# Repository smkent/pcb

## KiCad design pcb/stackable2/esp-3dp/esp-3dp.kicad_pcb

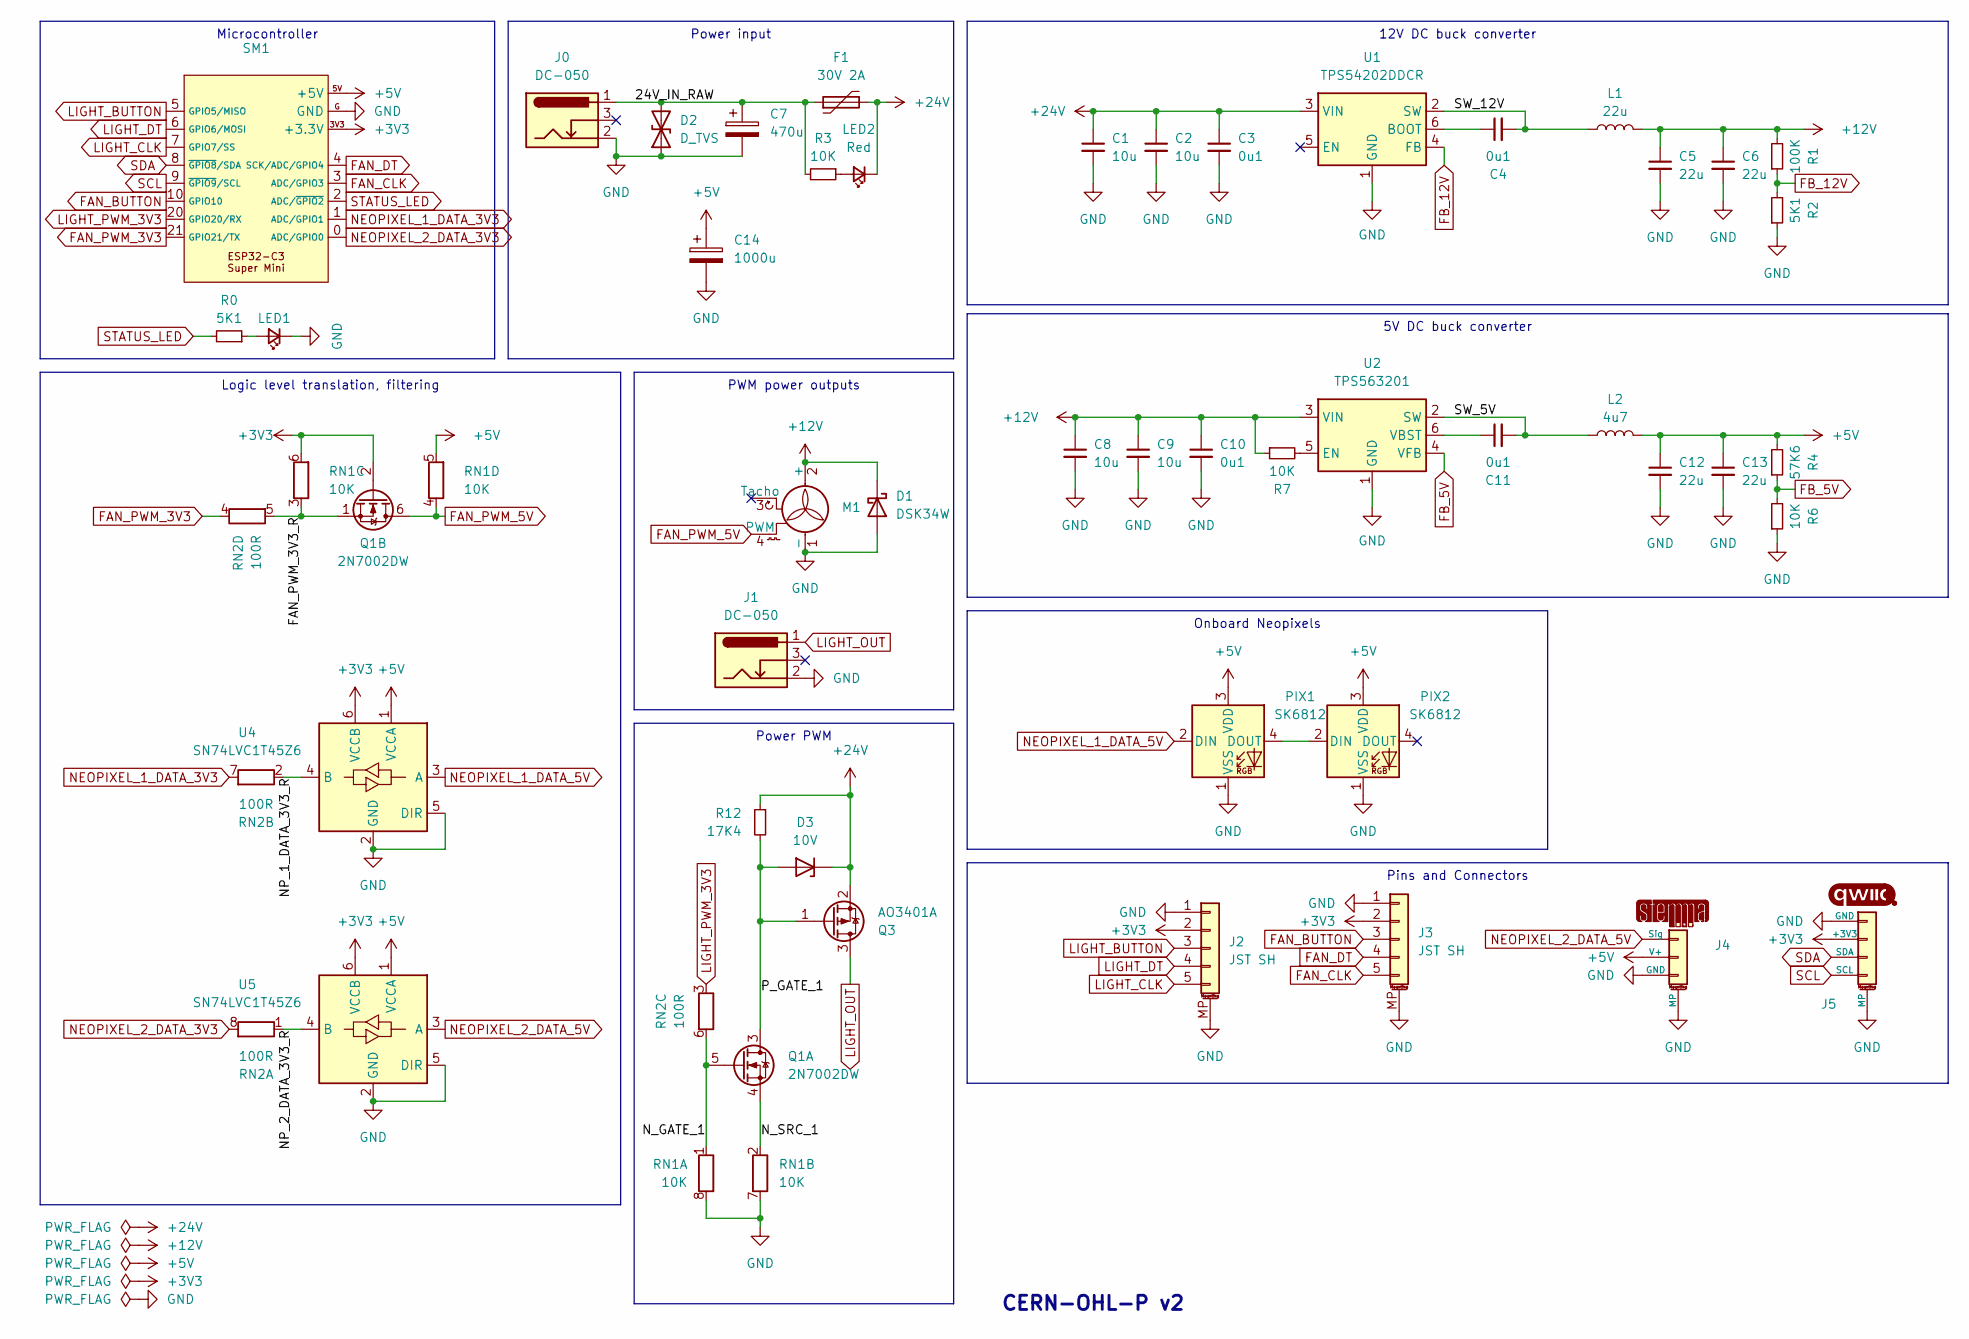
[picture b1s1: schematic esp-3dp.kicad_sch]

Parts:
C1, C2, C8, C9: 10u; C_0603_1608Metric
C3, C4, C10, C11: 0u1; C_0402_1005Metric
C5, C6: 22u; C_0805_2012Metric
C7: 470u; CP_Elec_8x10
C12, C13: 22u; C_0603_1608Metric
C14: 1000u; CP_Elec_8x10
D1: DSK34W; D_SOD-123F
D2: D_TVS; D_SOD-123F
D3: 10V; D_SOD-523
F1: 30V 2A; Fuse_1812_4532Metric
J0, J1: DC-050; BarrelJack_DC-050_SMT_Horizontal
J2, J3: JST SH; JST_SH_SM05B-SRSS-TB_1x05-1MP_P1.00mm_Horizontal
J4: STEMMA-Signal; STEMMA-Signal-SMD-horizontal
J5: Qwiic; Qwiic-SMD-horizontal
L1: 22u; L_Power_7.0x6.6mm_0630
L2: 4u7; L_1008_2520Metric
LED1: LED_Small; LED_0603_1608Metric
LED2: Red; LED_0402_1005Metric
M1: KF2510; FanPinHeader_1x04_P2.54mm_Horizontal
PIX1, PIX2: SK6812; LED_SK6812_PLCC4_5.0x5.0mm_P3.2mm
Q1: 2N7002DW; SOT-363_SC-70-6_HandSolder; LCSC Part C5190214
Q3: AO3401A; SOT-23
R0: 5K1; R_0603_1608Metric
R1: 100K; R_0402_1005Metric
R2: 5K1; R_0402_1005Metric
R3, R6, R7: 10K; R_0402_1005Metric
R4: 57K6; R_0402_1005Metric
R12: 17K4; R_0603_1608Metric
RN1: 10K; R_Array_Convex_4x0603_HandSolder
RN2: 100R; R_Array_Convex_4x0603_HandSolder
SM1: ESP32-C3-Super-Mini-Castellated-SMD-only
U1: TPS54202DDCR; SOT-23-6; LCSC Part C191884
U2: TPS563201; SOT-23-6
U4, U5: SN74LVC1T45Z6; SOT-563; LCSC Part C441819

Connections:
+3V3: J2.2, J3.2, J5.2 (+3V3), Q1.2 (G), RN1.6 (R3.2), SM1.3V3 (+3.3V), U4.6 (VCCB), U5.6 (VCCB)
+5V: C12.1, C13.1, C14.1, J4.2 (V+), L2.2, PIX1.3 (VDD), PIX2.3 (VDD), R4.2, RN1.5 (R4.2), SM1.5V (+5V), U4.1 (VCCA), U5.1 (VCCA)
+12V: C5.1, C6.1, C8.1, C9.1, C10.1, D1.1 (K), L1.2, M1.2 (+), R1.2, R7.1, U2.3 (VIN)
+24V: C1.1, C2.1, C3.1, D3.1 (K), F1.2, LED2.1 (K), Q3.2 (S), R12.1, U1.3 (VIN)
/24V_IN_RAW: C7.1, D2.2 (A2), F1.1, J0.1, R3.2
/FAN_PWM_3V3_R: Q1.1 (S), RN1.3 (R3.1), RN2.5 (R4.2)
/NP_1_DATA_3V3_R: RN2.2 (R2.1), U4.4 (B)
/NP_2_DATA_3V3_R: RN2.1 (R1.1), U5.4 (B)
/N_GATE_1: Q1.5 (G), RN1.1 (R1.1), RN2.6 (R3.2)
/N_SRC_1: Q1.4 (S), RN1.2 (R2.1)
/P_GATE_1: D3.2 (A), Q1.3 (D), Q3.1 (G), R12.2
/SW_5V: C11.2, L2.1, U2.2 (SW)
/SW_12V: C4.2, L1.1, U1.2 (SW)
FAN_BUTTON: J3.3, SM1.10 (GPIO10)
FAN_CLK: J3.5, SM1.3 (ADC/GPIO3)
FAN_DT: J3.4, SM1.4 (SCK/ADC/GPIO4)
FAN_PWM_3V3: RN2.4 (R4.1), SM1.21 (GPIO21/TX)
FAN_PWM_5V: M1.4 (PWM), Q1.6 (D), RN1.4 (R4.1)
FB_5V: R4.1, R6.2, U2.4 (VFB)
FB_12V: R1.1, R2.2, U1.4 (FB)
GND: C1.2, C2.2, C3.2, C5.2, C6.2, C7.2, C8.2, C9.2, C10.2, C12.2, C13.2, C14.2, D1.2 (A), D2.1 (A1), J0.2, J1.2, J2.1, J2.MP (MountPin), J3.1, J3.MP (MountPin), J4.3 (GND), J4.MP, J5.1 (GND), J5.MP, LED1.1 (K), M1.1 (-), PIX1.1 (VSS), PIX2.1 (VSS), R2.1, R6.1, RN1.7 (R2.2), RN1.8 (R1.2), SM1.G (GND), U1.1 (GND), U2.1 (GND), U4.2 (GND), U4.5 (DIR), U5.2 (GND), U5.5 (DIR)
LIGHT_BUTTON: J2.3, SM1.5 (GPIO5/MISO)
LIGHT_CLK: J2.5, SM1.7 (GPIO7/SS)
LIGHT_DT: J2.4, SM1.6 (GPIO6/MOSI)
LIGHT_OUT: J1.1, Q3.3 (D)
LIGHT_PWM_3V3: RN2.3 (R3.1), SM1.20 (GPIO20/RX)
NEOPIXEL_1_DATA_3V3: RN2.7 (R2.2), SM1.1 (ADC/GPIO1)
NEOPIXEL_1_DATA_5V: PIX1.2 (DIN), U4.3 (A)
NEOPIXEL_2_DATA_3V3: RN2.8 (R1.2), SM1.0 (ADC/GPIO0)
NEOPIXEL_2_DATA_5V: J4.1 (Sig), U5.3 (A)
unnamed: LED1.2 (A), R0.1
unnamed: LED2.2 (A), R3.1
unnamed: PIX1.4 (DOUT), PIX2.2 (DIN)
unnamed: C4.1, U1.6 (BOOT)
unnamed: R7.2, U2.5 (EN)
unnamed: C11.1, U2.6 (VBST)
SCL: J5.4 (SCL), SM1.9 (~GPIO9/SCL)
SDA: J5.3 (SDA), SM1.8 (~GPIO8/SDA)
STATUS_LED: R0.2, SM1.2 (ADC/~GPIO2)

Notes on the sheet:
5V DC buck converter
Power input
12V DC buck converter
Microcontroller
PWM power outputs
Onboard Neopixels
Pins and Connectors
Logic level translation, filtering
Power PWM
CERN-OHL-P v2

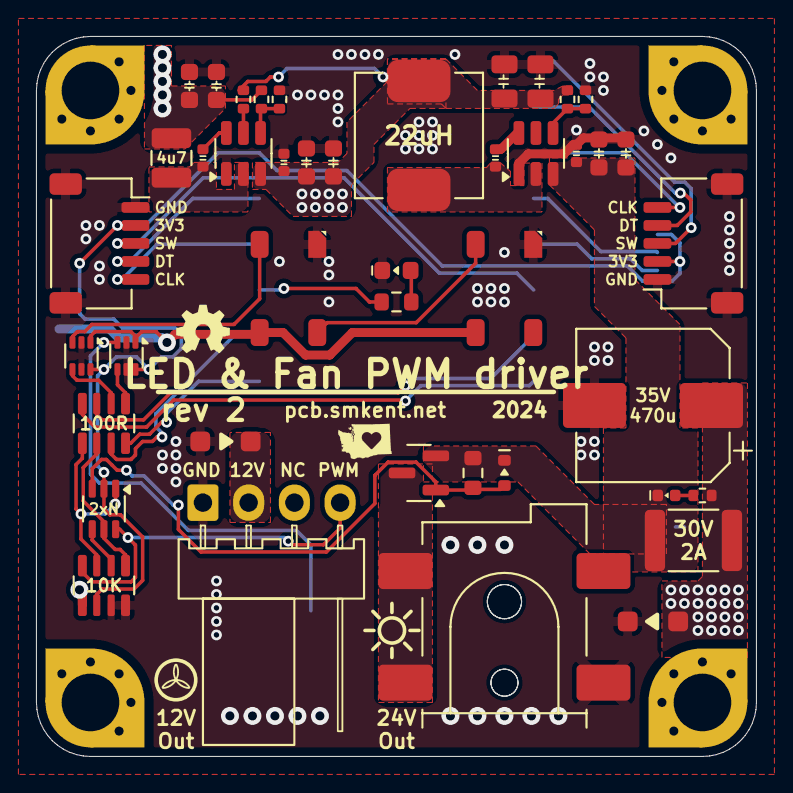
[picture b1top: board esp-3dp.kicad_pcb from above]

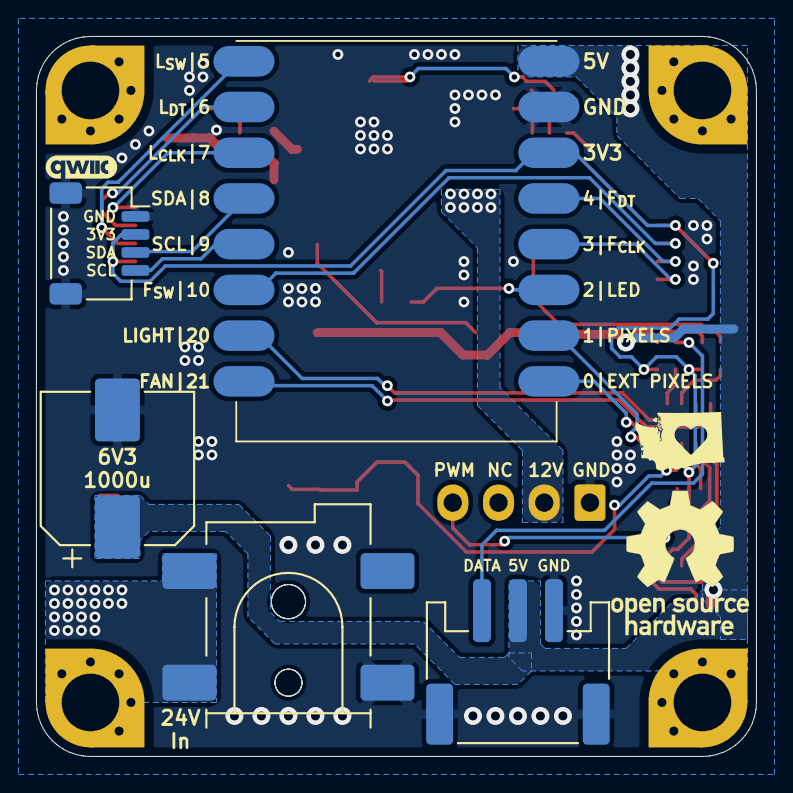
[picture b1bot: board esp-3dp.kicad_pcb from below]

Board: 2 copper layers, 40.0 x 40.0 mm, 52 parts (5 on the bottom side), 39 nets.

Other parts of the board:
MH_NE: MountingHole_3.2mm_M3_Pad_Via_corner_compact
MH_NW: MountingHole_3.2mm_M3_Pad_Via_corner_compact
MH_SE: MountingHole_3.2mm_M3_Pad_Via_corner_compact
MH_SW: MountingHole_3.2mm_M3_Pad_Via_corner_compact

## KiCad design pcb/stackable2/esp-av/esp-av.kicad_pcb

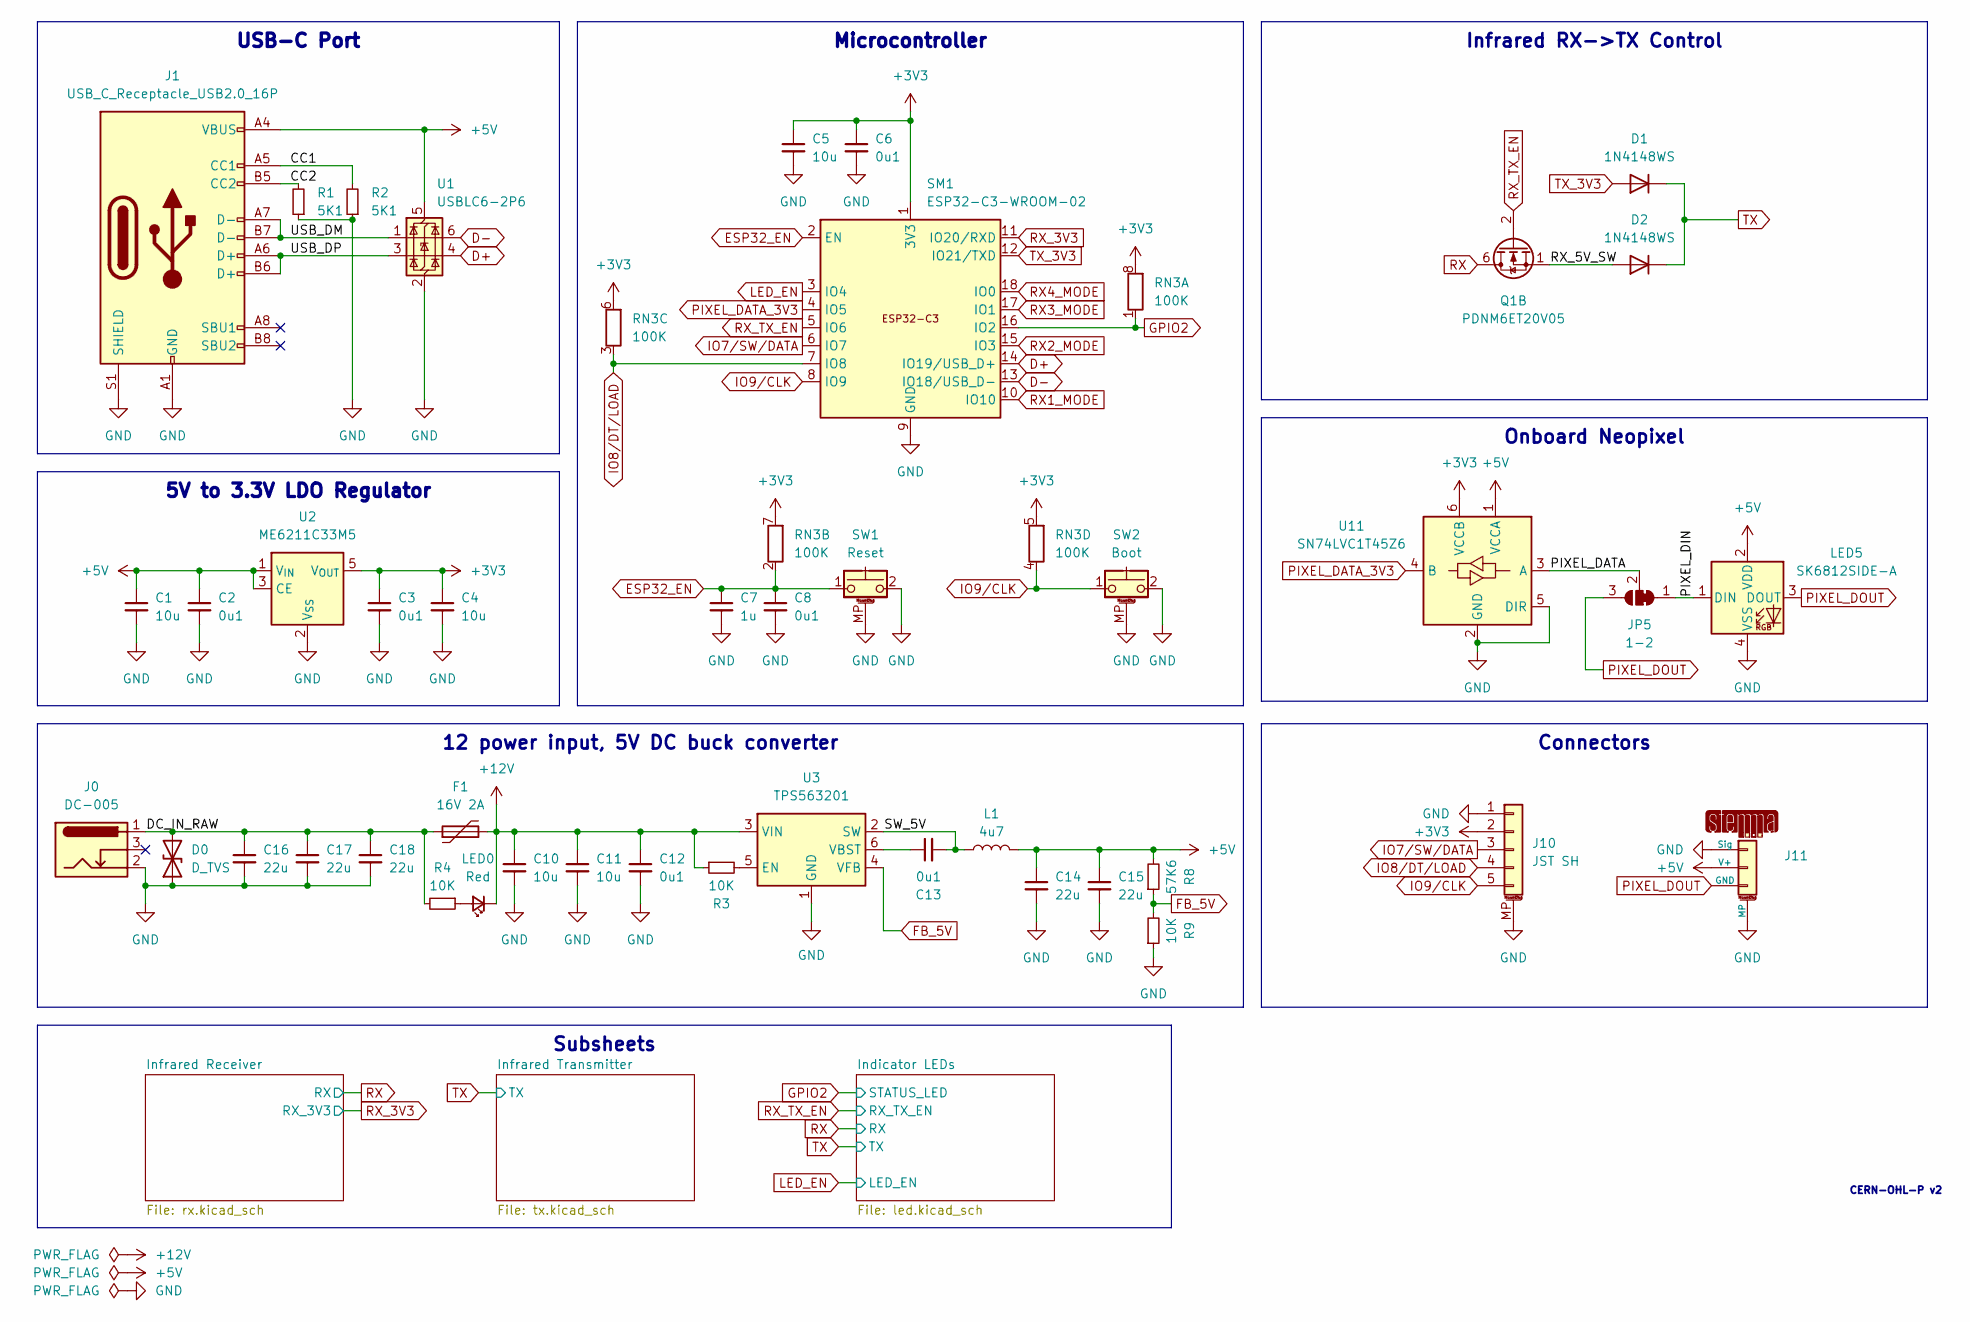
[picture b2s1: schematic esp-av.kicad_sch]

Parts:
C1, C4, C5, C10, C11: 10u; C_0603_1608Metric
C2, C3, C6, C8, C12, C13: 0u1; C_0603_1608Metric
C7: 1u; C_0603_1608Metric
C14, C15, C16, C17, C18: 22u; C_0603_1608Metric
D0: D_TVS; D_SOD-123F; LCSC Part C7473216
D1, D2: 1N4148WS; D_SOD-323
F1: 16V 2A; Fuse_1206_3216Metric; LCSC Part C2982271
J0: DC-005; BarrelJack_DC-005_THT_Horizontal
J1: USB_C_Receptacle_USB2.0_16P; USB_C_Receptacle_GCT_USB4105-xx-A_16P_TopMnt_Horizontal; LCSC Part C2765186
J10: JST SH; JST_SH_SM05B-SRSS-TB_1x05-1MP_P1.00mm_Horizontal
J11: STEMMA-Signal; STEMMA-Signal-SMD-horizontal
JP5: 1-2; SolderJumper-3_P1.3mm_Bridged12_RoundedPad1.0x1.5mm
L1: 4u7; L_1008_2520Metric; LCSC Part C22471106
LED0: Red; LED_0603_1608Metric
LED5: SK6812SIDE-A; LED_SK6812SIDE-A_4.0x1.6mm; LCSC Part C2890037
Q1: PDNM6ET20V05; SOT-563; LCSC Part C918811
R1, R2: 5K1; R_0603_1608Metric
R3, R4, R9: 10K; R_0603_1608Metric
R8: 57K6; R_0603_1608Metric
RN3: 100K; R_Array_Convex_4x0603_HandSolder
SM1: ESP32-C3-WROOM-02
SW1: Reset; SW_Push_1P1T-MP_NO_4.6x3mm_Horizontal
SW2: Boot; SW_Push_1P1T_NO_3.3x3.3mm_MP
U1: USBLC6-2P6; SOT-666; LCSC Part C29780639
U2: ME6211C33M5; SOT-23-5; LCSC Part C82942
U3: TPS563201; SOT-23-6; LCSC Part C116592
U11: SN74LVC1T45Z6; SOT-563; LCSC Part C441819

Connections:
+3V3: C3.1, C4.1, C5.1, C6.1, J10.2, RN3.5 (R4.2), RN3.6 (R3.2), RN3.7 (R2.2), RN3.8 (R1.2), SM1.1 (3V3), U2.5 (V_{OUT}), U11.6 (VCCB); also elsewhere on the board
+5V: C1.1, C2.1, C14.1, C15.1, J1.A4 (VBUS), J1.A9 (VBUS), J1.B4 (VBUS), J1.B9 (VBUS), J11.2 (V+), L1.2, LED5.2 (VDD), R8.2, U1.5 (VBUS), U2.1 (V_{IN}), U2.3 (CE), U11.1 (VCCA); also elsewhere on the board
+12V: C10.1, C11.1, C12.1, F1.2, LED0.1 (K), R3.1, U3.3 (VIN)
/CC1: J1.A5 (CC1), R2.2
/CC2: J1.B5 (CC2), R1.2
/DC_IN_RAW: C16.1, C17.1, C18.1, D0.2 (A2), F1.1, J0.1, R4.2
/PIXEL_DATA: JP5.2 (C), U11.3 (A)
/PIXEL_DIN: JP5.1 (A), LED5.1 (DIN)
/RX_5V_SW: D2.2 (A), Q1.1 (S)
/SW_5V: C13.2, L1.1, U3.2 (SW)
/USB_DM: J1.A7 (D-), J1.B7 (D-), U1.1 (I/O1)
/USB_DP: J1.A6 (D+), J1.B6 (D+), U1.3 (I/O2)
D+: SM1.14 (IO19/USB_D+), U1.4 (I/O2)
D-: SM1.13 (IO18/USB_D-), U1.6 (I/O1)
ESP32_EN: C7.1, C8.1, RN3.2 (R2.1), SM1.2 (EN), SW1.1
FB_5V: R8.1, R9.2, U3.4 (VFB)
GND: C1.2, C2.2, C3.2, C4.2, C5.2, C6.2, C7.2, C8.2, C10.2, C11.2, C12.2, C14.2, C15.2, C16.2, C17.2, C18.2, D0.1 (A1), J0.2, J1.A1 (GND), J1.A12 (GND), J1.B1 (GND), J1.B12 (GND), J1.S1 (SHIELD), J10.1, J10.MP (MountPin), J11.1 (Sig), J11.MP, LED5.4 (VSS), R1.1, R2.1, R9.1, SM1.9 (GND), SM1.19 (GND), SW1.2, SW1.MP (MountPin), SW2.2, SW2.MP (MountPin), U1.2 (GND), U2.2 (V_{SS}), U3.1 (GND), U11.2 (GND), U11.5 (DIR); also elsewhere on the board
GPIO2: RN3.1 (R1.1), SM1.16 (IO2); also elsewhere on the board
IO7/SW/DATA: J10.3, SM1.6 (IO7)
IO8/DT/LOAD: J10.4, RN3.3 (R3.1), SM1.7 (IO8)
IO9/CLK: J10.5, RN3.4 (R4.1), SM1.8 (IO9), SW2.1
LED_EN: SM1.3 (IO4); also elsewhere on the board
unnamed: LED0.2 (A), R4.1
unnamed: R3.2, U3.5 (EN)
unnamed: C13.1, U3.6 (VBST)
PIXEL_DATA_3V3: SM1.4 (IO5), U11.4 (B)
PIXEL_DOUT: J11.3 (GND), JP5.3 (B), LED5.3 (DOUT)
RX: Q1.6 (D); also elsewhere on the board
RX1_MODE: SM1.10 (IO10); also elsewhere on the board
RX2_MODE: SM1.15 (IO3); also elsewhere on the board
RX3_MODE: SM1.17 (IO1); also elsewhere on the board
RX4_MODE: SM1.18 (IO0); also elsewhere on the board
RX_3V3: SM1.11 (IO20/RXD); also elsewhere on the board
RX_TX_EN: Q1.2 (G), SM1.5 (IO6); also elsewhere on the board
TX: D1.1 (K), D2.1 (K); also elsewhere on the board
TX_3V3: D1.2 (A), SM1.12 (IO21/TXD)

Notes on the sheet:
5V to 3.3V LDO Regulator
Connectors
12 power input, 5V DC buck converter
Onboard Neopixel
Subsheets
Infrared RX->TX Control
USB-C Port
Microcontroller
CERN-OHL-P v2

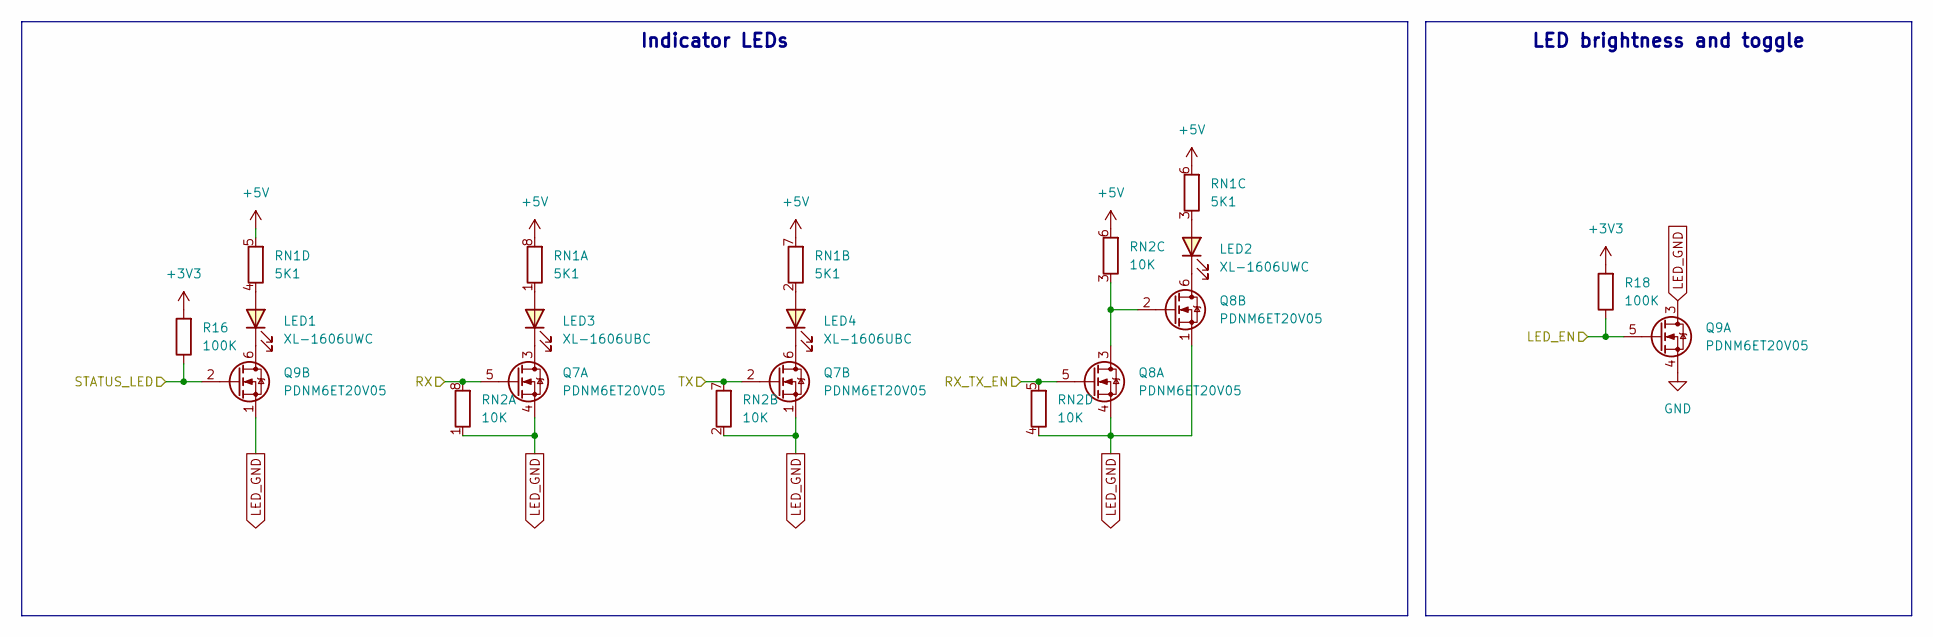
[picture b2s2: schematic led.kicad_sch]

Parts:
LED1, LED2: XL-1606UWC; LED_SideEmitter_1.7x1.1mm; LCSC Part C965866
LED3, LED4: XL-1606UBC; LED_SideEmitter_1.7x1.1mm; LCSC Part C965865
Q7, Q8, Q9: PDNM6ET20V05; SOT-563; LCSC Part C918811
R16, R18: 100K; R_0603_1608Metric
RN1: 5K1; R_Array_Convex_4x0603_HandSolder
RN2: 10K; R_Array_Convex_4x0603_HandSolder

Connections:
+3V3: R16.2, R18.2; also elsewhere on the board
+5V: RN1.5 (R4.2), RN1.6 (R3.2), RN1.7 (R2.2), RN1.8 (R1.2), RN2.6 (R3.2); also elsewhere on the board
GND: Q9.4 (S); also elsewhere on the board
GPIO2: Q9.2 (G), R16.1; also elsewhere on the board
LED_EN: Q9.5 (G), R18.1; also elsewhere on the board
LED_GND: Q7.1 (S), Q7.4 (S), Q8.1 (S), Q8.4 (S), Q9.1 (S), Q9.3 (D), RN2.1 (R1.1), RN2.2 (R2.1), RN2.4 (R4.1)
unnamed: LED1.2 (A), RN1.4 (R4.1)
unnamed: LED1.1 (K), Q9.6 (D)
unnamed: LED2.2 (A), RN1.3 (R3.1)
unnamed: LED2.1 (K), Q8.6 (D)
unnamed: LED3.2 (A), RN1.1 (R1.1)
unnamed: LED3.1 (K), Q7.3 (D)
unnamed: LED4.2 (A), RN1.2 (R2.1)
unnamed: LED4.1 (K), Q7.6 (D)
unnamed: Q8.2 (G), Q8.3 (D), RN2.3 (R3.1)
RX: Q7.5 (G), RN2.8 (R1.2); also elsewhere on the board
RX_TX_EN: Q8.5 (G), RN2.5 (R4.2); also elsewhere on the board
TX: Q7.2 (G), RN2.7 (R2.2); also elsewhere on the board

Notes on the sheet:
LED brightness and toggle
Indicator LEDs

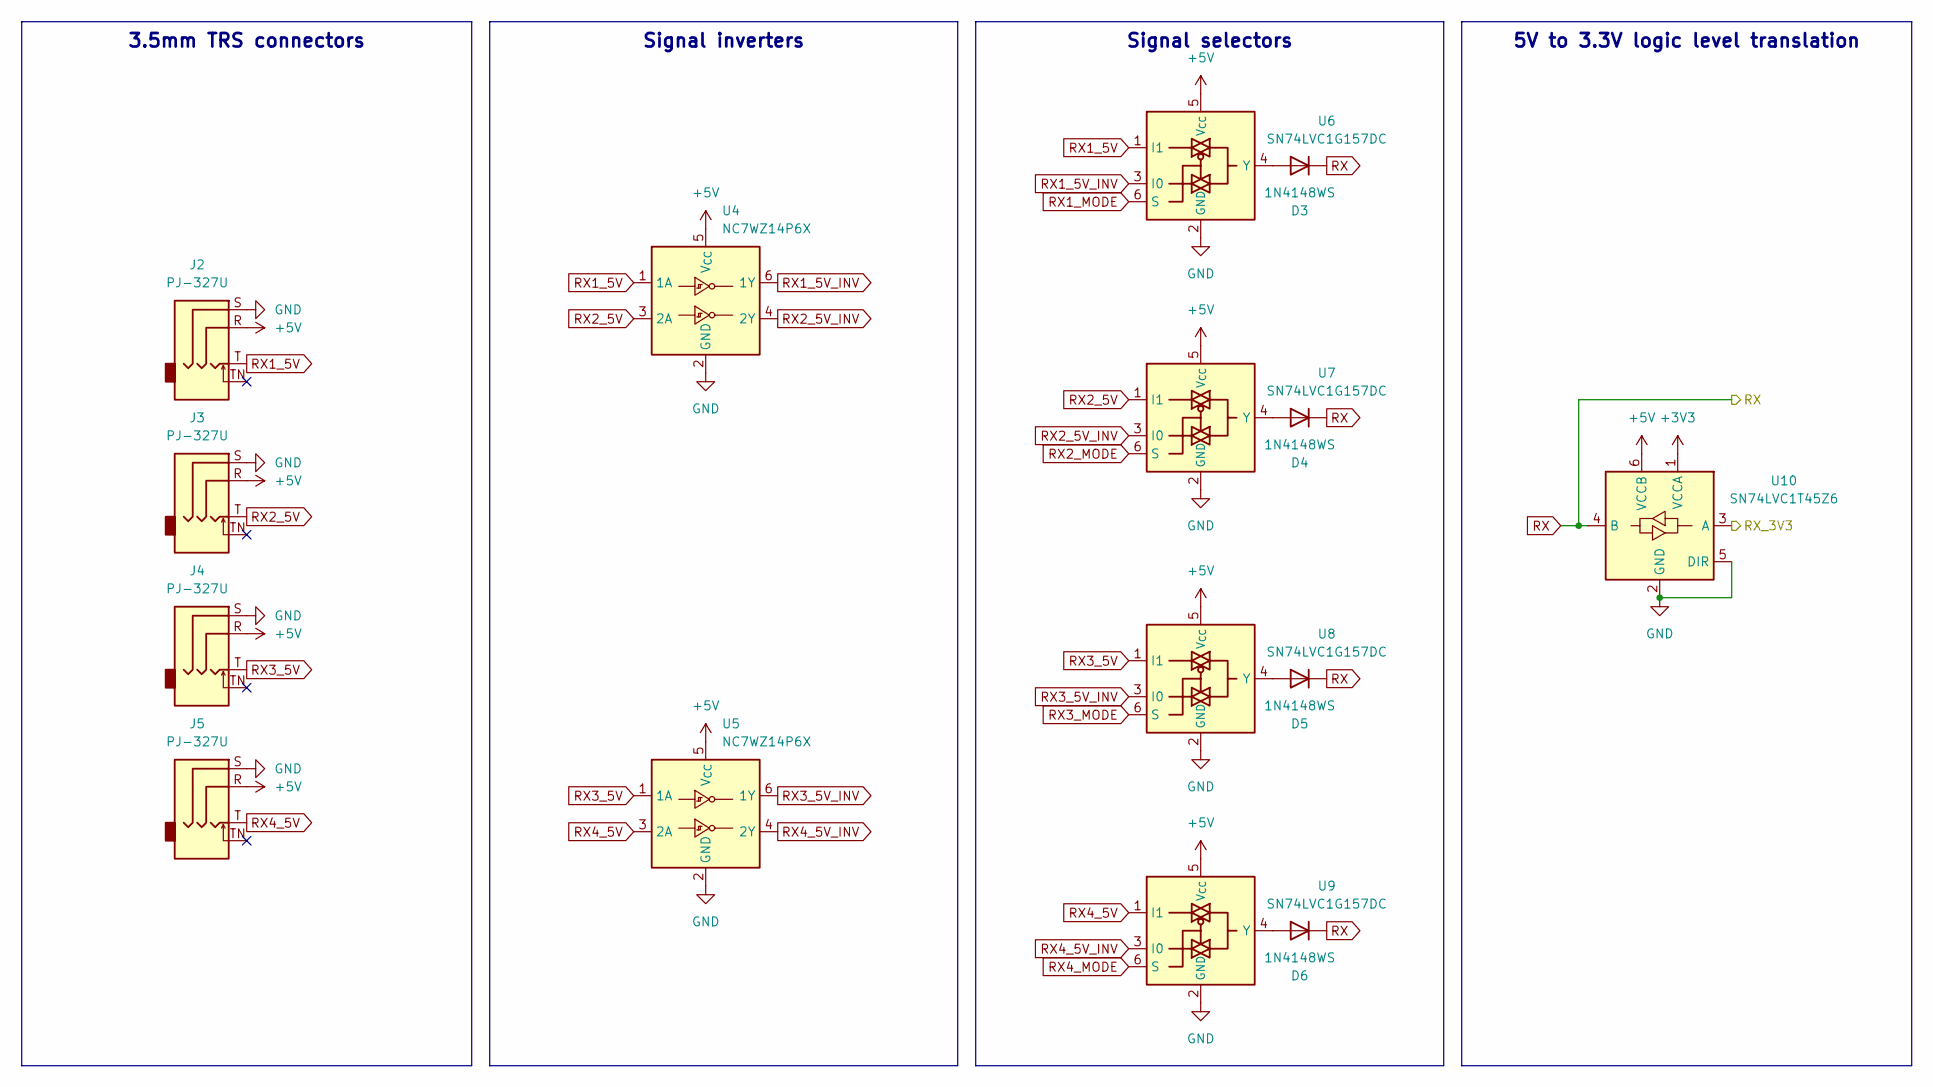
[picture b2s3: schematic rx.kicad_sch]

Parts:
D3, D4, D5, D6: 1N4148WS; D_SOD-323
J2, J3, J4, J5: PJ-327U; Jack_3.5mm_PJ-327U-SMT_Horizontal; LCSC Part C397453
U4, U5: NC7WZ14P6X; SOT-363_SC-70-6_HandSolder; LCSC Part C5207816
U6, U7, U8, U9: SN74LVC1G157DC; SOT-363_SC-70-6_HandSolder; LCSC Part C22469913
U10: SN74LVC1T45Z6; SOT-563; LCSC Part C441819

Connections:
+3V3: U10.1 (VCCA); also elsewhere on the board
+5V: J2.R, J3.R, J4.R, J5.R, U4.5 (V_{CC}), U5.5 (V_{CC}), U6.5 (V_{CC}), U7.5 (V_{CC}), U8.5 (V_{CC}), U9.5 (V_{CC}), U10.6 (VCCB); also elsewhere on the board
GND: J2.S, J3.S, J4.S, J5.S, U4.2 (GND), U5.2 (GND), U6.2 (GND), U7.2 (GND), U8.2 (GND), U9.2 (GND), U10.2 (GND), U10.5 (DIR); also elsewhere on the board
unnamed: D3.2 (A), U6.4 (Y)
unnamed: D4.2 (A), U7.4 (Y)
unnamed: D5.2 (A), U8.4 (Y)
unnamed: D6.2 (A), U9.4 (Y)
RX: D3.1 (K), D4.1 (K), D5.1 (K), D6.1 (K), U10.4 (B); also elsewhere on the board
RX1_5V: J2.T, U4.1 (1A), U6.1 (I1)
RX1_5V_INV: U4.6 (1Y), U6.3 (I0)
RX1_MODE: U6.6 (S); also elsewhere on the board
RX2_5V: J3.T, U4.3 (2A), U7.1 (I1)
RX2_5V_INV: U4.4 (2Y), U7.3 (I0)
RX2_MODE: U7.6 (S); also elsewhere on the board
RX3_5V: J4.T, U5.1 (1A), U8.1 (I1)
RX3_5V_INV: U5.6 (1Y), U8.3 (I0)
RX3_MODE: U8.6 (S); also elsewhere on the board
RX4_5V: J5.T, U5.3 (2A), U9.1 (I1)
RX4_5V_INV: U5.4 (2Y), U9.3 (I0)
RX4_MODE: U9.6 (S); also elsewhere on the board
RX_3V3: U10.3 (A); also elsewhere on the board

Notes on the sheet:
Signal inverters
3.5mm TRS connectors
5V to 3.3V logic level translation
Signal selectors

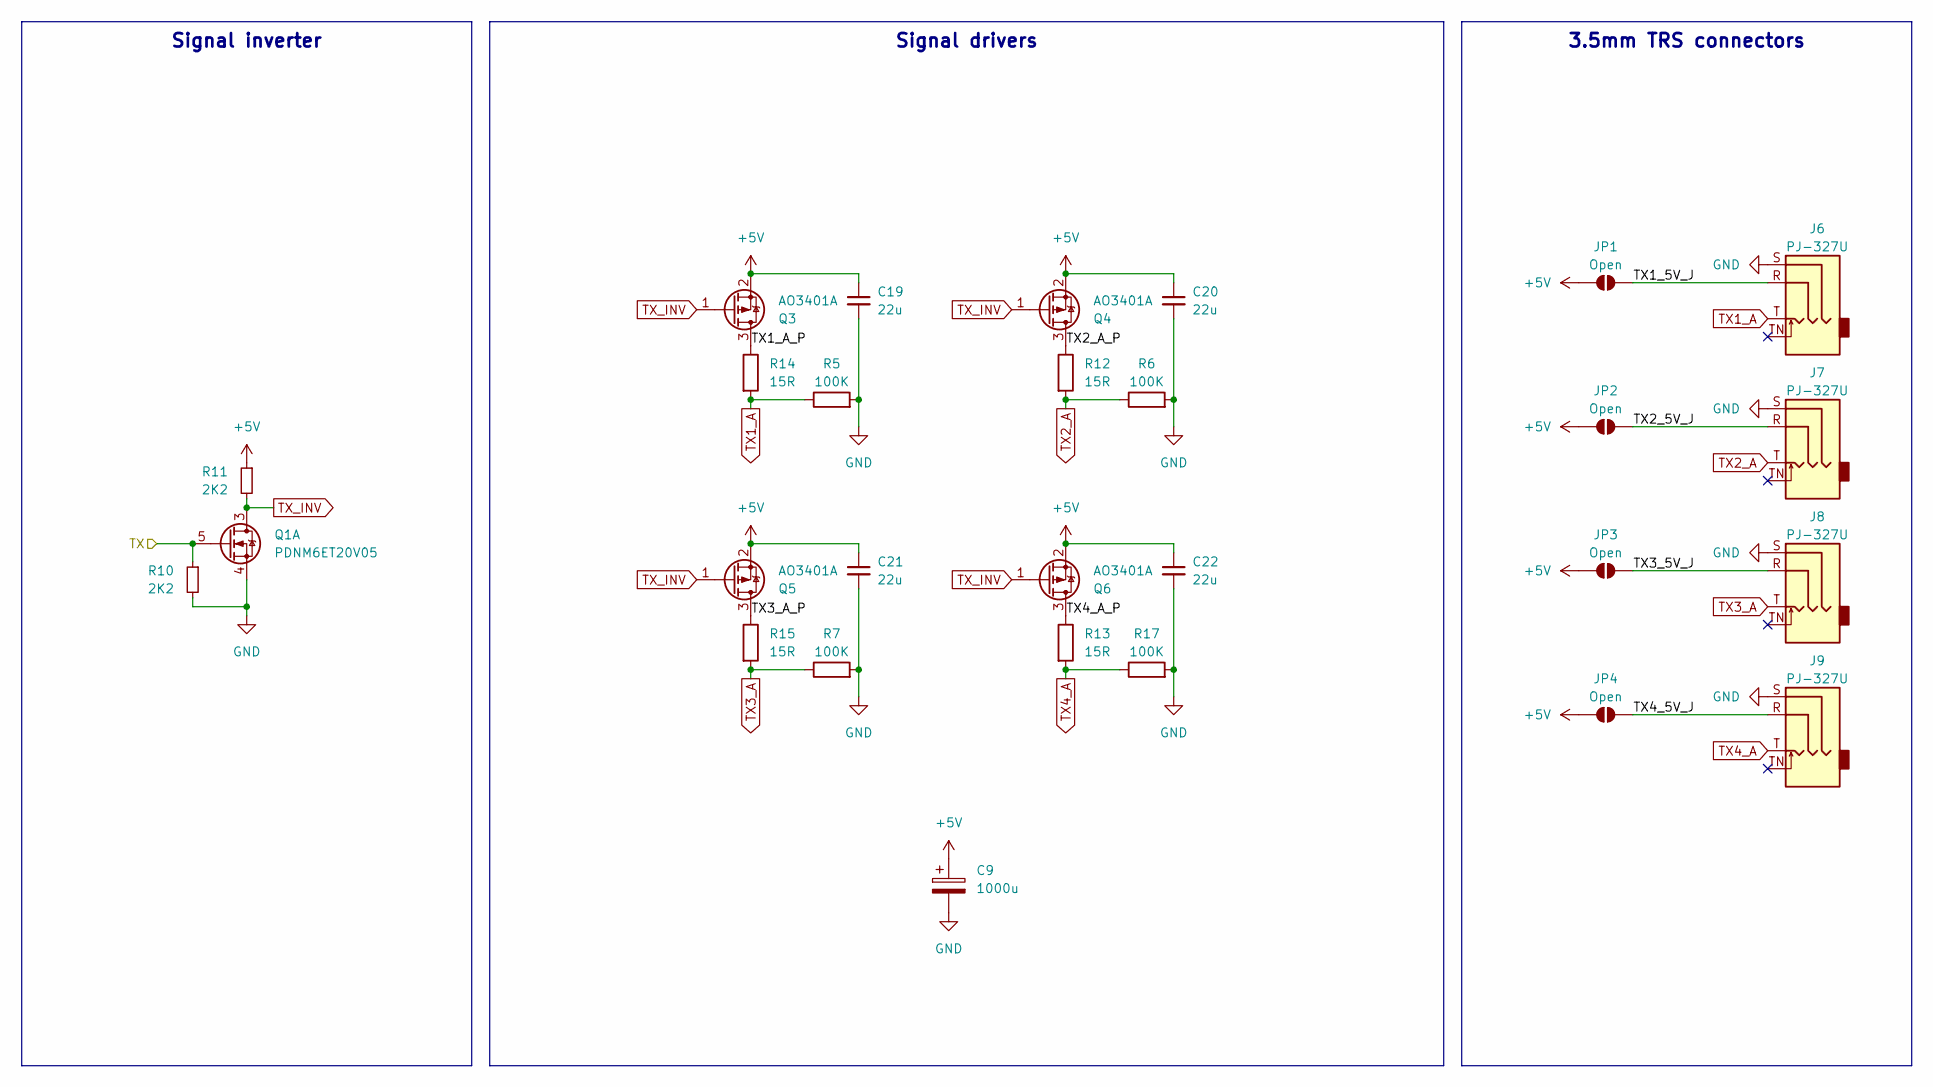
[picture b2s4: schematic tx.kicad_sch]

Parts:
C9: 1000u; CP_Elec_8x10
C19, C20, C21, C22: 22u; C_0603_1608Metric
J6, J7, J8, J9: PJ-327U; Jack_3.5mm_PJ-327U-SMT_Horizontal; LCSC Part C397453
JP1, JP2, JP3, JP4: Open; SolderJumper-2_P1.3mm_Open_TrianglePad1.0x1.5mm
Q1: PDNM6ET20V05; SOT-563; LCSC Part C918811
Q3, Q4, Q5, Q6: AO3401A; SOT-23
R5, R6, R7, R17: 100K; R_0603_1608Metric
R10, R11: 2K2; R_0603_1608Metric
R12, R13, R14, R15: 15R; R_1206_3216Metric

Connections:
+5V: C9.1, C19.1, C20.1, C21.1, C22.1, JP1.1 (A), JP2.1 (A), JP3.1 (A), JP4.1 (A), Q3.2 (S), Q4.2 (S), Q5.2 (S), Q6.2 (S), R11.1; also elsewhere on the board
/Infrared Transmitter/TX1_5V_J: J6.R, JP1.2 (B)
/Infrared Transmitter/TX1_A_P: Q3.3 (D), R14.1
/Infrared Transmitter/TX2_5V_J: J7.R, JP2.2 (B)
/Infrared Transmitter/TX2_A_P: Q4.3 (D), R12.1
/Infrared Transmitter/TX3_5V_J: J8.R, JP3.2 (B)
/Infrared Transmitter/TX3_A_P: Q5.3 (D), R15.1
/Infrared Transmitter/TX4_5V_J: J9.R, JP4.2 (B)
/Infrared Transmitter/TX4_A_P: Q6.3 (D), R13.1
GND: C9.2, C19.2, C20.2, C21.2, C22.2, J6.S, J7.S, J8.S, J9.S, Q1.4 (S), R5.2, R6.2, R7.2, R10.2, R17.2; also elsewhere on the board
TX: Q1.5 (G), R10.1; also elsewhere on the board
TX1_A: J6.T, R5.1, R14.2
TX2_A: J7.T, R6.1, R12.2
TX3_A: J8.T, R7.1, R15.2
TX4_A: J9.T, R13.2, R17.1
TX_INV: Q1.3 (D), Q3.1 (G), Q4.1 (G), Q5.1 (G), Q6.1 (G), R11.2

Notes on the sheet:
Signal inverter
3.5mm TRS connectors
Signal drivers

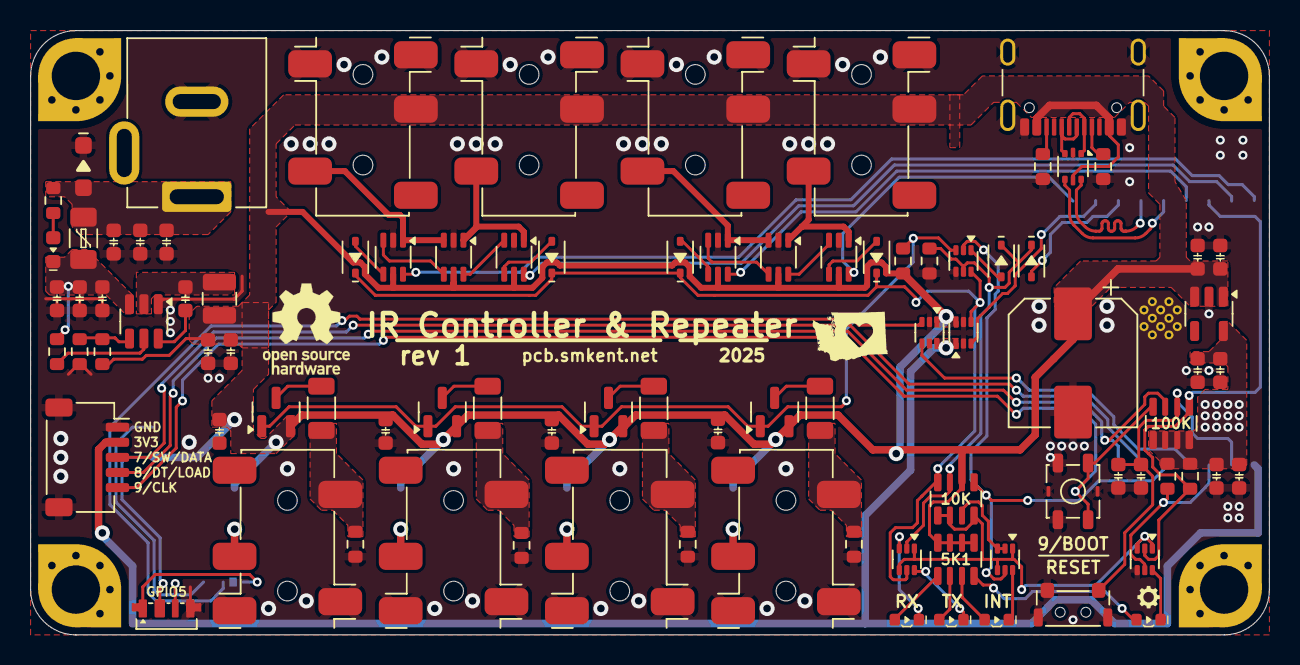
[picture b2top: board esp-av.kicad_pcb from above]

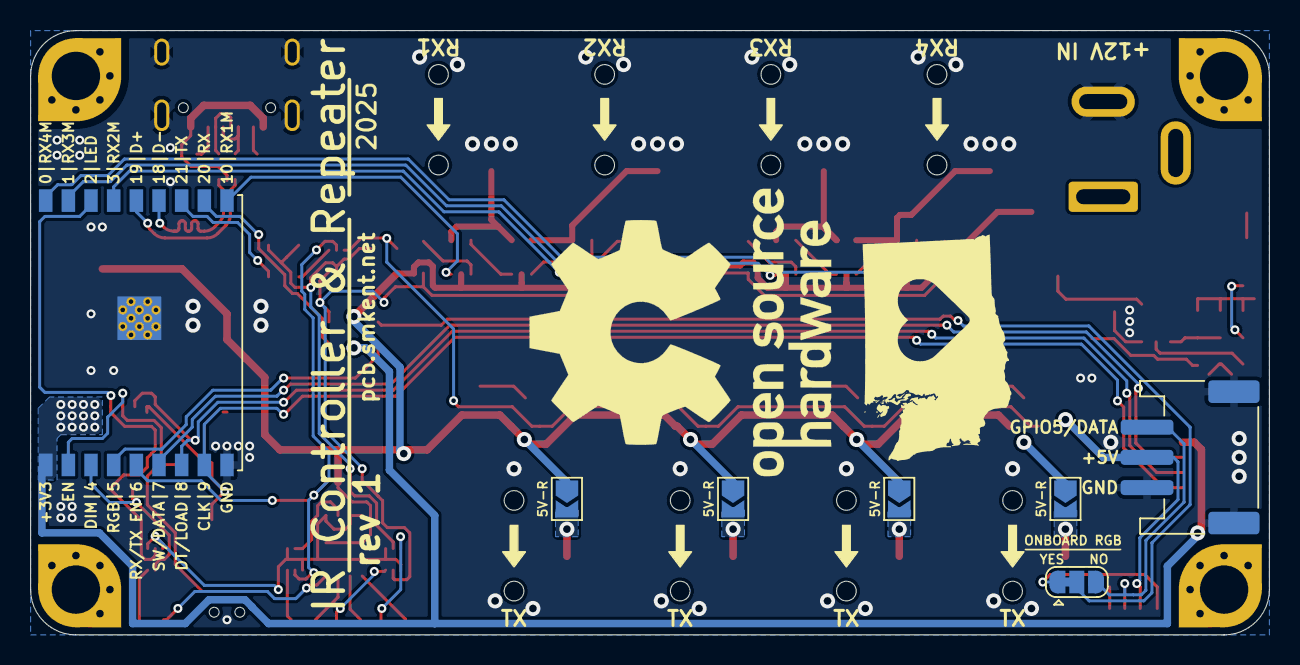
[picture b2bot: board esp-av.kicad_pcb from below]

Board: 2 copper layers, 82.0 x 40.0 mm, 97 parts (7 on the bottom side), 71 nets.
